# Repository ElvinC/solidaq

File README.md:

# SoliDAQ

Super basic ADC/data logger board based on an Adafruit feather rp2040 dev board and an AD7124-4 24-bit ADC.

## Data storage format

```
typedef struct SensorLog {
    uint8_t header; // 'S' = 0x53. Keep track of used memory
    uint8_t log_id; // Log ID and marker for used memory.
    uint32_t time; // Time in ms
    int16_t adc_temp; // Cold junction temp in 0.01 deg celsius
    int16_t core_temp; // rp2040 temp in 0.01 deg celsius
    int32_t lc; // Loadcell, ratiometric in millionth (0.000001)
    int32_t tc1; // Thermocouple 1, value in nanovolts
    int32_t tc2; // Thermocouple 2, value in nanovolts
    int32_t ps; // 4-20 mA pressure. Value in nanoamps
    uint8_t delta_time;
    uint8_t log_percent; // Percent of the log that is full
    uint16_t vbat; // Battery voltage in 0.01V
} sensor_log_t;
```

csv representation example:

```
id,time[ms],tref[C],lc[mV/V],tc1[C],tc2[C],ps[mA]              
1,1374,21.0,0.670,32.8,20.7,-0.004       
```

With 32 megabytes of memory: 2.7 hours of logging time.

## USB Drive mode

The device emulates a FAT16 filesystem.

Some android phones can't open this natively. You can use e.g. the ZUGate app to connect to it.

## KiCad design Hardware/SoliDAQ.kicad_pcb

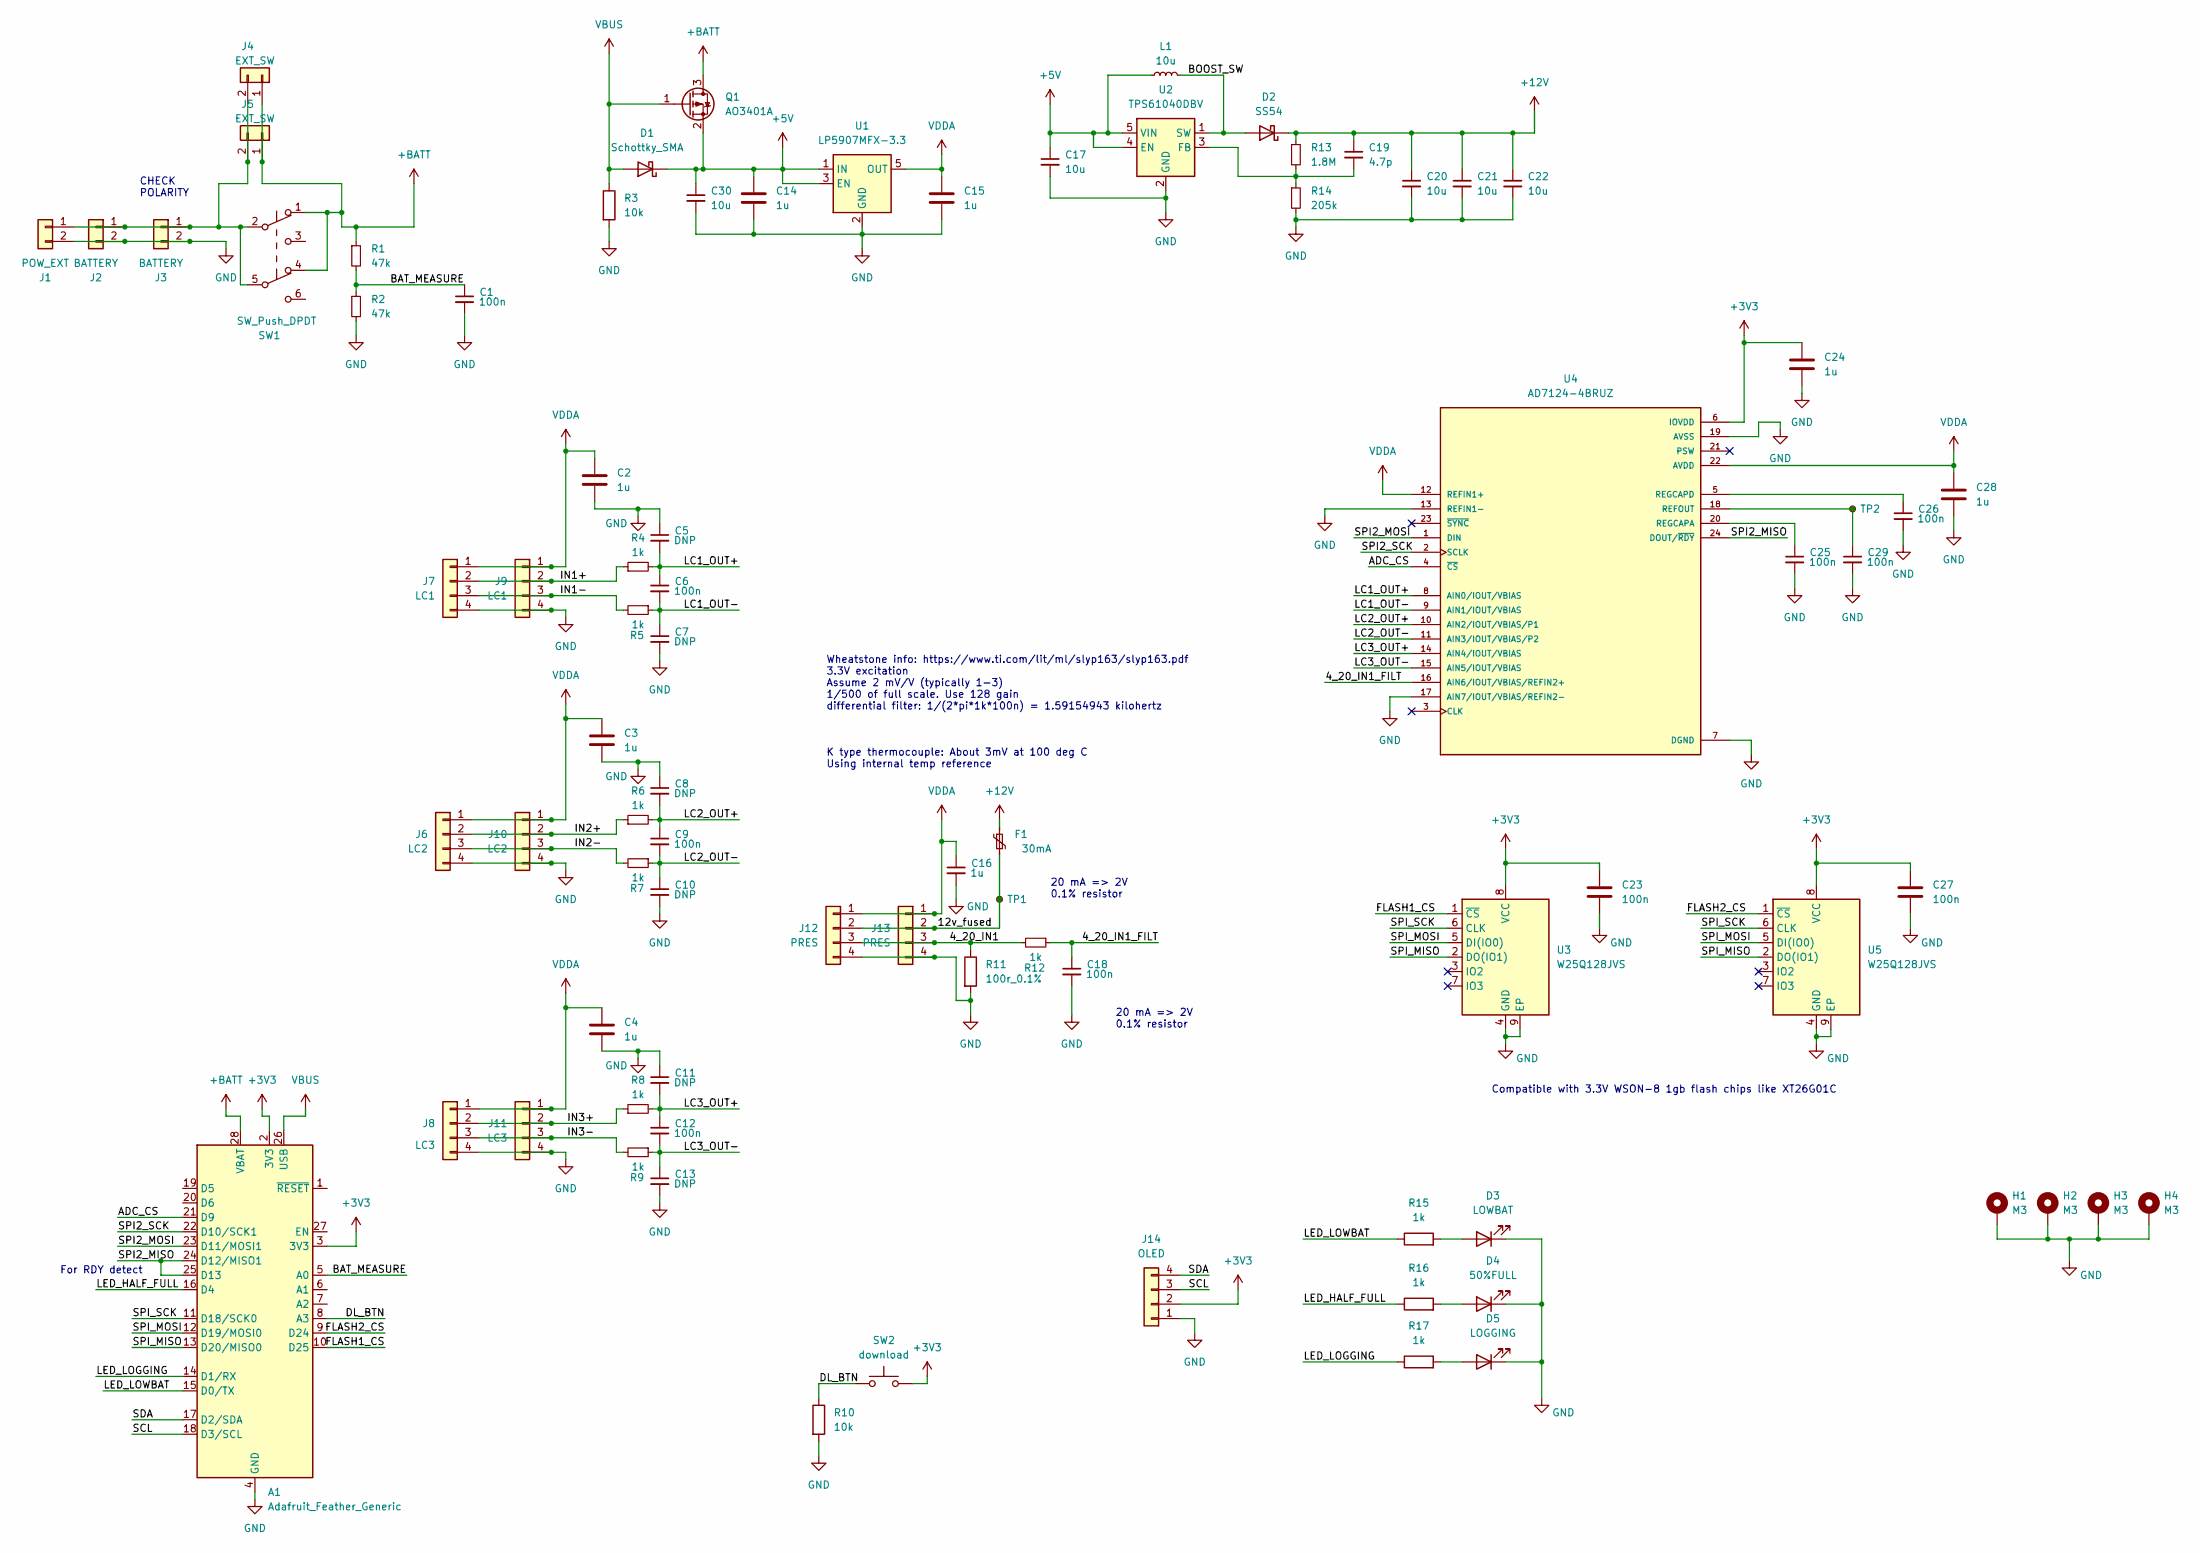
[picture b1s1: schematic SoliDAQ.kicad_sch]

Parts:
A1: Adafruit_Feather_Generic; Adafruit_Feather
C1, C6, C9, C12, C18, C23, C25, C26, C27, C29: 100n; C_0603_1608Metric
C2, C3, C4, C14, C15, C16, C24, C28: 1u; C_0603_1608Metric
C5, C7, C8, C10, C11, C13: DNP; C_0603_1608Metric
C17, C20, C21, C22, C30: 10u; C_0805_2012Metric
C19: 4.7p; C_0603_1608Metric
D1: Schottky_SMA; D_SMA
D2: SS54; D_SMA
D3: LOWBAT; LED_0603_1608Metric
D4: 50%FULL; LED_0603_1608Metric
D5: LOGGING; LED_0603_1608Metric
F1: 30mA; Fuse_0603_1608Metric; LCSC C7472504
H1, H2, H3, H4: M3; MountingHole_3.2mm_M3_Pad_Via
J1: POW_EXT; TerminalBlock_TE_282834-2_1x02_P2.54mm_Horizontal
J2: BATTERY; JST_PH_S2B-PH-K_1x02_P2.00mm_Horizontal
J3: BATTERY; BatteryHolder_Keystone_1042_1x18650; LCSC C2988620
J4: EXT_SW; TerminalBlock_TE_282834-2_1x02_P2.54mm_Horizontal
J5: EXT_SW; CONN2_S02B-PASK-2_JST
J6: LC2; TerminalBlock_TE_282834-4_1x04_P2.54mm_Horizontal
J7: LC1; TerminalBlock_TE_282834-4_1x04_P2.54mm_Horizontal
J8: LC3; TerminalBlock_TE_282834-4_1x04_P2.54mm_Horizontal
J9: LC1; JST_S04B-PASK-2_LF__SN_
J10: LC2; JST_S04B-PASK-2_LF__SN_
J11: LC3; JST_S04B-PASK-2_LF__SN_
J12: PRES; TerminalBlock_TE_282834-4_1x04_P2.54mm_Horizontal
J13: PRES; JST_S04B-PASK-2_LF__SN_
J14: OLED; i2c_oled
L1: 10u; L_Sunlord_MWSA0603S; LCSC C132141
Q1: AO3401A; SOT-23
R1, R2: 47k; R_0603_1608Metric
R3, R10: 10k; R_0603_1608Metric
R4, R5, R6, R7, R8, R9, R12, R15, R16, R17: 1k; R_0603_1608Metric
R11: 100r_0.1%; R_0603_1608Metric; LCSC C394538
R13: 1.8M; R_0603_1608Metric
R14: 205k; R_0603_1608Metric
SW1: SW_Push_DPDT; SW_DPDT_MST22D18G2
SW2: download; SW_Push_1P1T_XKB_TS-1187A
TP1, TP2: TestPoint_Small; TestPoint_Pad_D1.0mm
U1: LP5907MFX-3.3; SOT-23-5
U2: TPS61040DBV; SOT-23-5
U3, U5: W25Q128JVS; SOIC-8_EP_5.23x5.23mm_P1.27mm
U4: AD7124-4BRUZ; SOP65P640X120-24N; PARTREV D

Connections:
+3V3: A1.2 (3V3), A1.3 (3V3), C23.1, C24.1, C27.1, J14.2, SW2.2, U3.8 (VCC), U4.6 (IOVDD), U5.8 (VCC)
+5V: C14.1, C17.1, C30.1, D1.1 (K), L1.1, Q1.2 (S), U1.1 (IN), U1.3 (EN), U2.4 (EN), U2.5 (VIN)
+12V: C19.1, C20.1, C21.1, C22.1, D2.1 (K), F1.1, R13.1
+BATT: A1.28 (VBAT), J4.1, J5.1, Q1.3 (D), R1.1, SW1.1 (A), SW1.4 (A)
/4_20_IN1: J12.3, J13.3, R11.1, R12.2
/4_20_IN1_FILT: C18.1, R12.1, U4.16 (AIN6/IOUT/VBIAS/REFIN2+)
/12v_fused: F1.2, J12.2, J13.2, TP1.1
/ADC_CS: A1.21 (D9), U4.4 (~CS)
/BAT_MEASURE: A1.5 (A0), C1.1, R1.2, R2.1
/BOOST_SW: D2.2 (A), L1.2, U2.1 (SW)
/DL_BTN: A1.8 (A3), R10.1, SW2.1
/FLASH1_CS: A1.10 (D25), U3.1 (~CS)
/FLASH2_CS: A1.9 (D24), U5.1 (~CS)
/IN1+: J7.2, J9.2, R4.1
/IN1-: J7.3, J9.3, R5.2
/IN2+: J6.2, J10.2, R6.1
/IN2-: J6.3, J10.3, R7.2
/IN3+: J8.2, J11.2, R8.1
/IN3-: J8.3, J11.3, R9.2
/LC1_OUT+: C5.2, C6.1, R4.2, U4.8 (AIN0/IOUT/VBIAS)
/LC1_OUT-: C6.2, C7.1, R5.1, U4.9 (AIN1/IOUT/VBIAS)
/LC2_OUT+: C8.2, C9.1, R6.2, U4.10 (AIN2/IOUT/VBIAS/P1)
/LC2_OUT-: C9.2, C10.1, R7.1, U4.11 (AIN3/IOUT/VBIAS/P2)
/LC3_OUT+: C11.2, C12.1, R8.2, U4.14 (AIN4/IOUT/VBIAS)
/LC3_OUT-: C12.2, C13.1, R9.1, U4.15 (AIN5/IOUT/VBIAS)
/LED_HALF_FULL: A1.16 (D4), R16.1
/LED_LOGGING: A1.14 (D1/RX), R17.1
/LED_LOWBAT: A1.15 (D0/TX), R15.1
/SCL: A1.18 (D3/SCL), J14.3
/SDA: A1.17 (D2/SDA), J14.4
/SPI2_MISO: A1.24 (D12/MISO1), A1.25 (D13), U4.24 (DOUT/~RDY)
/SPI2_MOSI: A1.23 (D11/MOSI1), U4.1 (DIN)
/SPI2_SCK: A1.22 (D10/SCK1), U4.2 (SCLK)
/SPI_MISO: A1.13 (D20/MISO0), U3.2 (DO(IO1)), U5.2 (DO(IO1))
/SPI_MOSI: A1.12 (D19/MOSI0), U3.5 (DI(IO0)), U5.5 (DI(IO0))
/SPI_SCK: A1.11 (D18/SCK0), U3.6 (CLK), U5.6 (CLK)
GND: A1.4 (GND), C1.2, C2.2, C3.2, C4.2, C5.1, C7.2, C8.1, C10.2, C11.1, C13.2, C14.2, C15.2, C16.2, C17.2, C18.2, C20.2, C21.2, C22.2, C23.2, C24.2, C25.2, C26.2, C27.2, C28.2, C29.2, C30.2, D3.1 (K), D4.1 (K), D5.1 (K), H1.1, H2.1, H3.1, H4.1, J1.2, J2.2, J3.2, J6.4, J7.4, J8.4, J9.4, J10.4, J11.4, J12.4, J13.4, J14.1, R2.2, R3.2, R10.2, R11.2, R14.2, U1.2 (GND), U2.2 (GND), U3.4 (GND), U3.9 (EP), U4.7 (DGND), U4.13 (REFIN1-), U4.17 (AIN7/IOUT/VBIAS/REFIN2-), U4.19 (AVSS), U5.4 (GND), U5.9 (EP)
unnamed: D3.2 (A), R15.2
unnamed: D4.2 (A), R16.2
unnamed: D5.2 (A), R17.2
unnamed: J1.1, J2.1, J3.1, J4.2, J5.2, SW1.2 (B), SW1.5 (B)
unnamed: C19.2, R13.2, R14.1, U2.3 (FB)
unnamed: C29.1, TP2.1, U4.18 (REFOUT)
unnamed: C25.1, U4.20 (REGCAPA)
unnamed: C26.1, U4.5 (REGCAPD)
VBUS: A1.26 (USB), D1.2 (A), Q1.1 (G), R3.1
VDDA: C2.1, C3.1, C4.1, C15.1, C16.1, C28.1, J6.1, J7.1, J8.1, J9.1, J10.1, J11.1, J12.1, J13.1, U1.5 (OUT), U4.12 (REFIN1+), U4.22 (AVDD)

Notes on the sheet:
Compatible with 3.3V WSON-8 1gb flash chips like XT26G01C
20 mA => 2V 0.1% resistor
For RDY detect
K type thermocouple: About 3mV at 100 deg C Using internal temp reference
Wheatstone info: https://www.ti.com/lit/ml/slyp163/slyp163.pdf 3.3V excitation Assume 2 mV/V (typically 1-3) 1/500 of full scale. Use 128 gain differential filter: 1/(2*pi*1k*100n) = 1.59154943 kilohertz
CHECK POLARITY

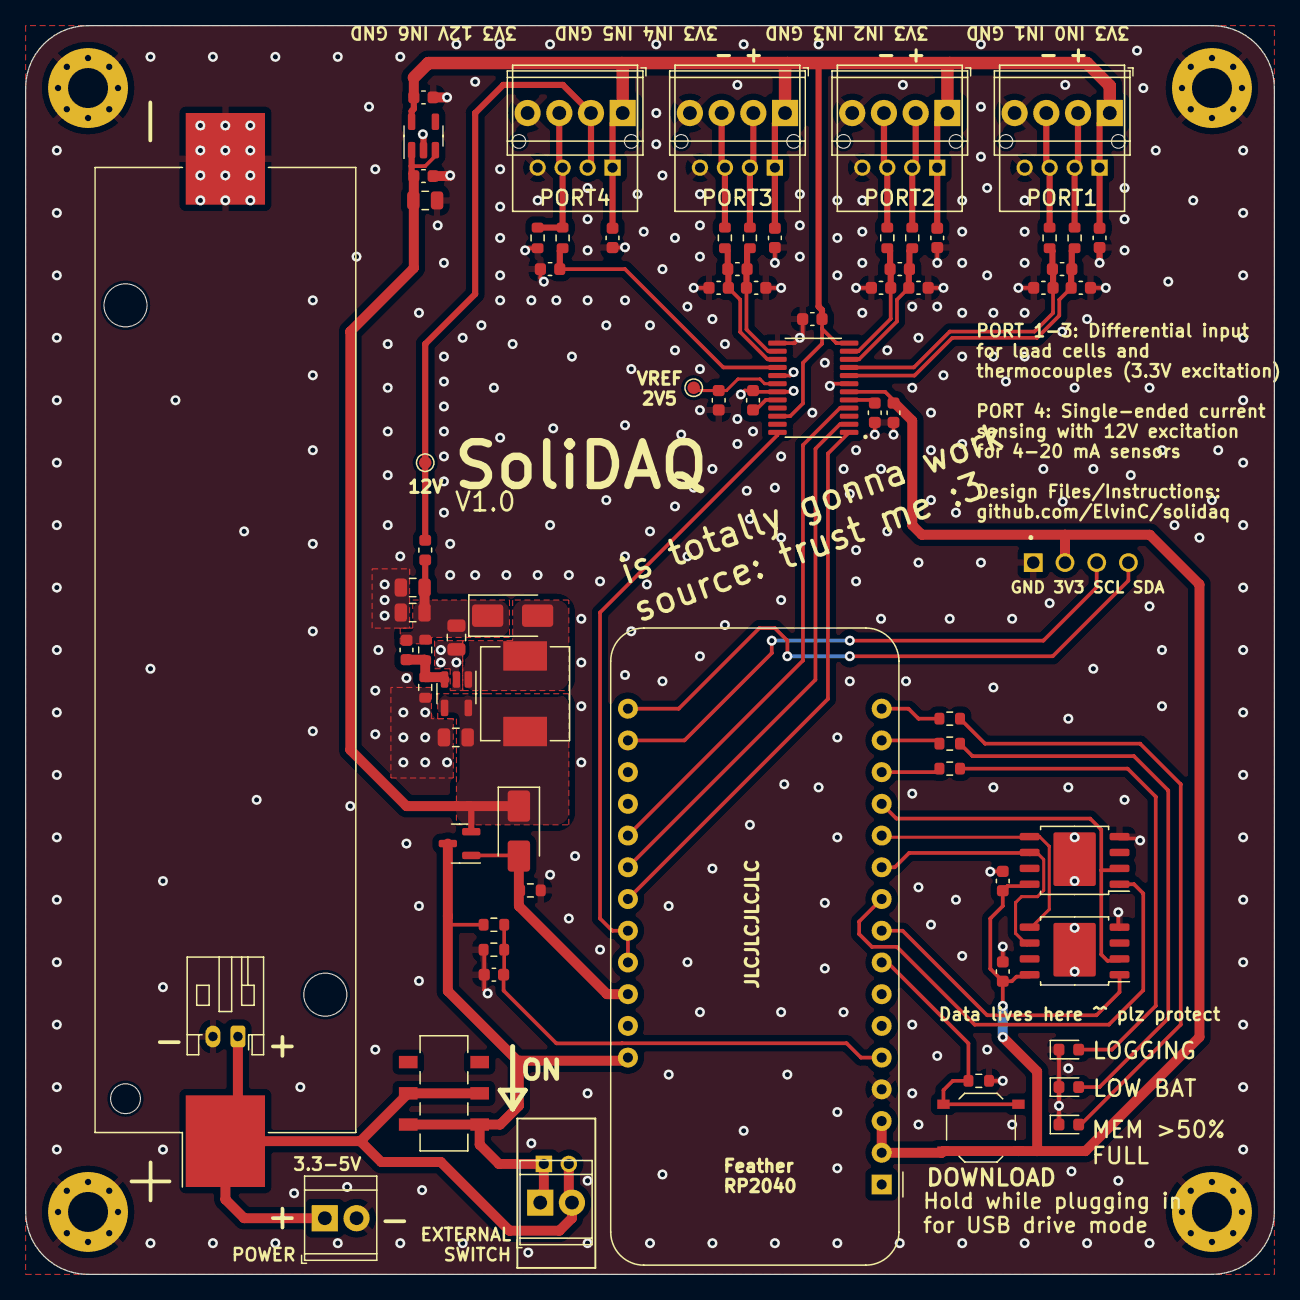
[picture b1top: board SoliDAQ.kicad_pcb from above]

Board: 2 copper layers, 100.0 x 100.0 mm, 83 parts (0 on the bottom side), 47 nets.

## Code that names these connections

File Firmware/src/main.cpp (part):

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
int VBAT_PIN = A0;
// For ADC
int ADC_CS = D9;
int SPI1_SCK = D10;
int SPI1_MOSI = D11;
int SPI1_MISO = D12;
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int SPI0_SCK = D18;
int SPI0_MOSI = D19;
int SPI0_MISO = D20;
int FLASH1_CS = D25;
int FLASH2_CS = D24;

// Misc pins
int LED_HALF_FULL = D6;
int LED_LOGGING = D1;
int LED_LOWBAT = D0;
int DOWNLOAD_PIN = A3;
int SDA_PIN = D2;
int SCL_PIN = D3;
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    // Set up pins
    pinMode(VBAT_PIN, INPUT);
    pinMode(DOWNLOAD_PIN, INPUT);
    pinMode(ADC_CS, INPUT);
    pinMode(ADC_RDY_MISO, INPUT);
    pinMode(LED_HALF_FULL, OUTPUT);
    pinMode(LED_LOGGING, OUTPUT);
    pinMode(LED_LOWBAT, OUTPUT);

    pinMode(SPI0_MOSI, OUTPUT);
    pinMode(SPI0_MISO, INPUT);
    pinMode(SPI0_SCK, OUTPUT);

    // SPI for flash
    pinMode(FLASH1_CS, OUTPUT);
    digitalWrite(FLASH1_CS, HIGH);
    pinMode(FLASH2_CS, OUTPUT);
    digitalWrite(FLASH2_CS, HIGH);
    SPI.setTX(SPI0_MOSI);
    SPI.setRX(SPI0_MISO);
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
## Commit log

2025-03-12 Add basic firmware
